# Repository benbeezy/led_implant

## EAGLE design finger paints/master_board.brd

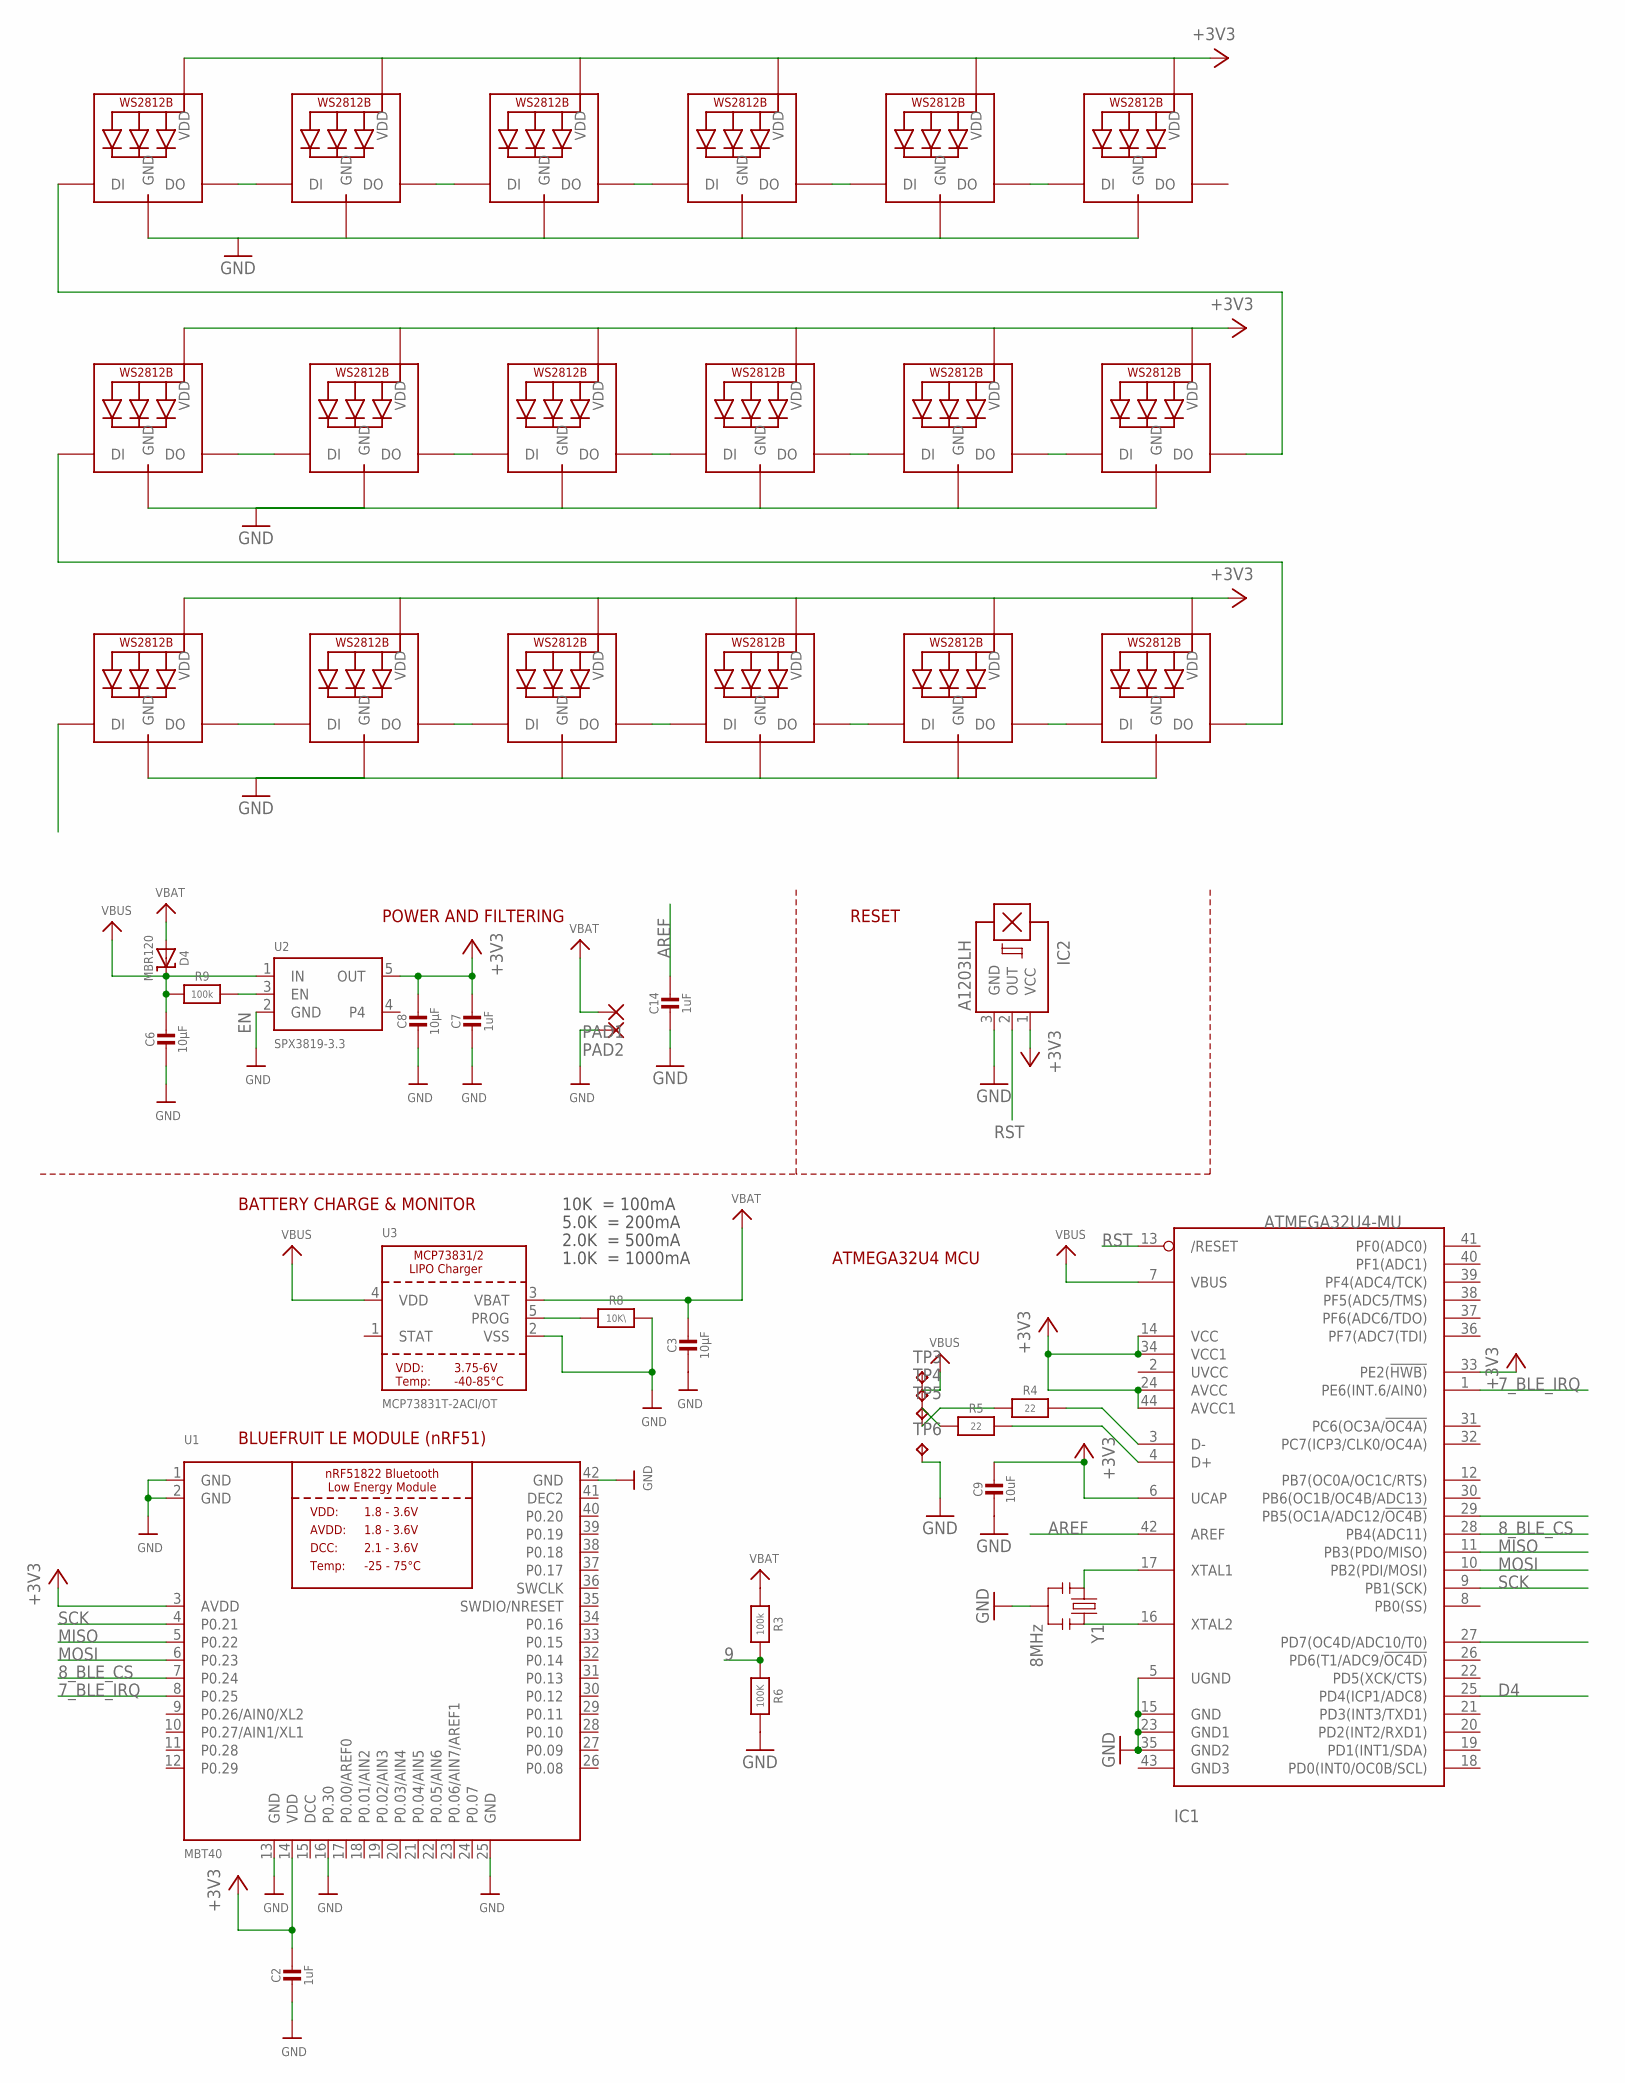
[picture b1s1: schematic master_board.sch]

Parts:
C2: 1uF; 0805-NO
C3, C6, C8: 10µF; 0805-NO
C7, C14: 1uF; 0603-NO
C9: 10uF; 0805-NO
D4: MBR120; SOD-123
IC1: ATMEGA32U4-MU; TQFN44_7MM
IC2: A1203LH; SOT23-W
LED1, LED2, LED3, LED4, LED5, LED6, LED7, LED8, LED9, LED10, LED11, LED12, LED13, LED14, LED15, LED16, LED17, LED18: WS2812B3535; LED3535
PAD1, PAD2: 2,54/1,1
R3, R9: 100k; 0603-NO
R4, R5: 22; 0603-NO
R6: 100K; _0603MP
R8: 10K\; 0603-NO
TP3, TP4, TP5, TP6: TPTP06SQ; TP06SQ
U1: MBT40; BLE_MODULE_RAYTAC_MDBT40
U2: SPX3819-3.3; SOT23-5
U3: MCP73831T-2ACI/OT; SOT23-5
Y1: 8MHz; RESONATOR-SMD

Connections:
6: IC1.27 (PD7(OC4D/ADC10/T0)), LED1.1 (DI)
7_BLE_IRQ: IC1.1 (PE6(INT.6/AIN0)), U1.8 (P0.25)
8_BLE_CS: IC1.28 (PB4(ADC11)), U1.7 (P0.24)
9: IC1.29 (PB5(OC1A/ADC12/!OC4B)), R3.2, R6.1
+3V3: C2.1, C7.1, C8.1, C9.1, IC1.6 (UCAP), IC1.14 (VCC), IC1.24 (AVCC), IC1.33 (PE2(!HWB)), IC1.34 (VCC1), IC1.44 (AVCC1), IC2.1 (VCC), LED1.2 (VDD), LED2.2 (VDD), LED3.2 (VDD), LED4.2 (VDD), LED5.2 (VDD), LED6.2 (VDD), LED7.2 (VDD), LED8.2 (VDD), LED9.2 (VDD), LED10.2 (VDD), LED11.2 (VDD), LED12.2 (VDD), LED13.2 (VDD), LED14.2 (VDD), LED15.2 (VDD), LED16.2 (VDD), LED17.2 (VDD), LED18.2 (VDD), U1.3 (AVDD), U1.14 (VDD), U2.5 (OUT)
AREF: C14.1, IC1.42 (AREF)
D4: IC1.25 (PD4(ICP1/ADC8))
D+: IC1.4 (D+), R5.2
D-: IC1.3 (D-), R4.2
DCC: U1.15 (DCC)
DEC2: U1.41 (DEC2)
DO: LED6.3 (DO), LED7.1 (DI)
EN: R9.2, U2.3 (EN)
GND: C2.2, C3.2, C6.2, C7.2, C8.2, C9.2, C14.2, IC1.5 (UGND), IC1.15 (GND), IC1.23 (GND1), IC1.35 (GND2), IC2.3 (GND), LED1.4 (GND), LED2.4 (GND), LED3.4 (GND), LED4.4 (GND), LED5.4 (GND), LED6.4 (GND), LED7.4 (GND), LED8.4 (GND), LED9.4 (GND), LED10.4 (GND), LED11.4 (GND), LED12.4 (GND), LED13.4 (GND), LED14.4 (GND), LED15.4 (GND), LED16.4 (GND), LED17.4 (GND), LED18.4 (GND), PAD2.1, R6.2, R8.2, TP6.TP, U1.1 (GND), U1.2 (GND), U1.13 (GND), U1.16 (P0.30), U1.25 (GND), U1.42 (GND), U2.2 (GND), U3.2 (VSS), Y1.2
MISO: IC1.11 (PB3(PDO/MISO)), U1.5 (P0.22)
MOSI: IC1.10 (PB2(PDI/MOSI)), U1.6 (P0.23)
unnamed: LED17.3 (DO), LED18.1 (DI)
unnamed: LED11.3 (DO), LED12.1 (DI)
unnamed: R8.1, U3.5 (PROG)
unnamed: LED16.3 (DO), LED17.1 (DI)
unnamed: LED15.3 (DO), LED16.1 (DI)
unnamed: LED1.3 (DO), LED2.1 (DI)
unnamed: LED2.3 (DO), LED3.1 (DI)
unnamed: LED3.3 (DO), LED4.1 (DI)
unnamed: LED4.3 (DO), LED5.1 (DI)
unnamed: IC1.16 (XTAL2), Y1.3
unnamed: IC1.17 (XTAL1), Y1.1
unnamed: LED5.3 (DO), LED6.1 (DI)
unnamed: LED7.3 (DO), LED8.1 (DI)
unnamed: R5.1, TP4.TP
unnamed: R4.1, TP5.TP
unnamed: LED8.3 (DO), LED9.1 (DI)
unnamed: LED9.3 (DO), LED10.1 (DI)
unnamed: LED10.3 (DO), LED11.1 (DI)
unnamed: LED14.3 (DO), LED15.1 (DI)
unnamed: LED13.3 (DO), LED14.1 (DI)
unnamed: LED12.3 (DO), LED13.1 (DI)
RST: IC1.13 (/RESET), IC2.2 (OUT)
SCK: IC1.9 (PB1(SCK)), U1.4 (P0.21)
VBAT: C3.1, D4.A, PAD1.1, R3.1, U3.3 (VBAT)
VBUS: C6.1, D4.C, IC1.7 (VBUS), R9.1, TP3.TP, U2.1 (IN), U3.4 (VDD)

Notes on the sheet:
POWER AND FILTERING
RESET
ATMEGA32U4 MCU
10K = 100mA
5.0K = 200mA
2.0K = 500mA
1.0K = 1000mA
BATTERY CHARGE & MONITOR
BLUEFRUIT LE MODULE (nRF51)

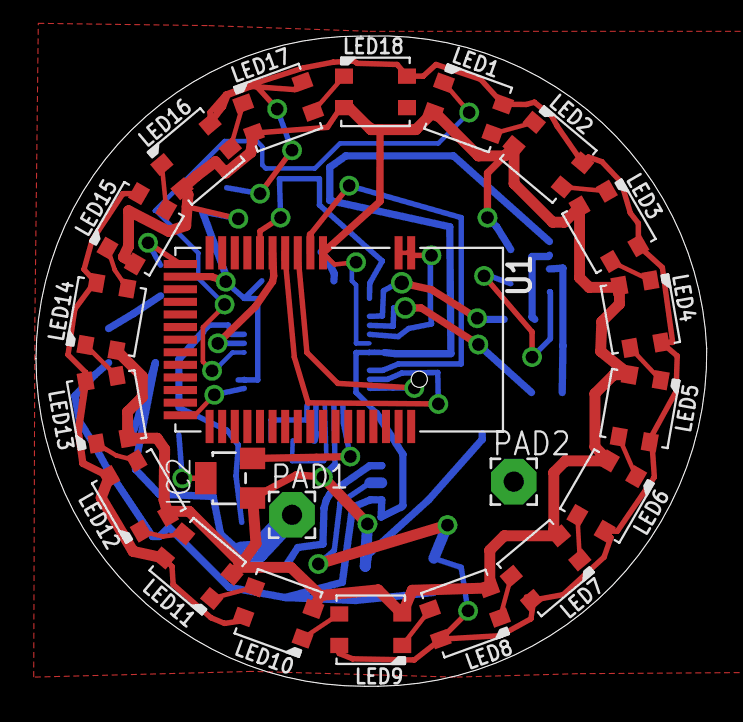
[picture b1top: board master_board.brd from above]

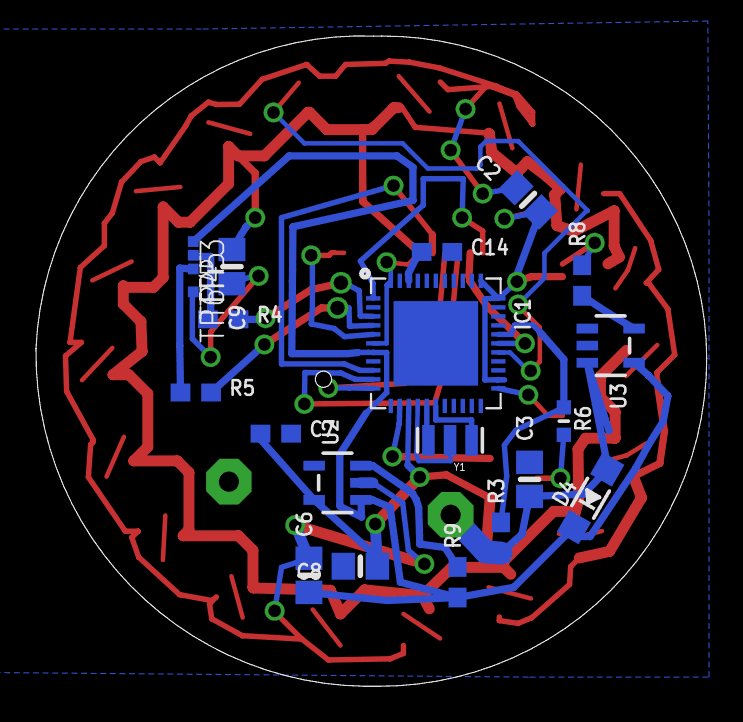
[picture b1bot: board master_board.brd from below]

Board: 2 copper layers, 37.3 x 36.1 mm, 44 parts (22 on the bottom side), 38 nets.

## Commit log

2015-12-29 init
2015-12-29 removing things

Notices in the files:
parts and their libraries:
microbuilder: This work is placed in the public domain, and may be freely used for commercial and non-commercial work with the following conditions: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
SparkFun: Licensing: CC v3.0 Share-Alike You are welcome to use this library for commercial purposes.
